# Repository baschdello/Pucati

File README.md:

# Pucati
Pump controller with adjustable timer

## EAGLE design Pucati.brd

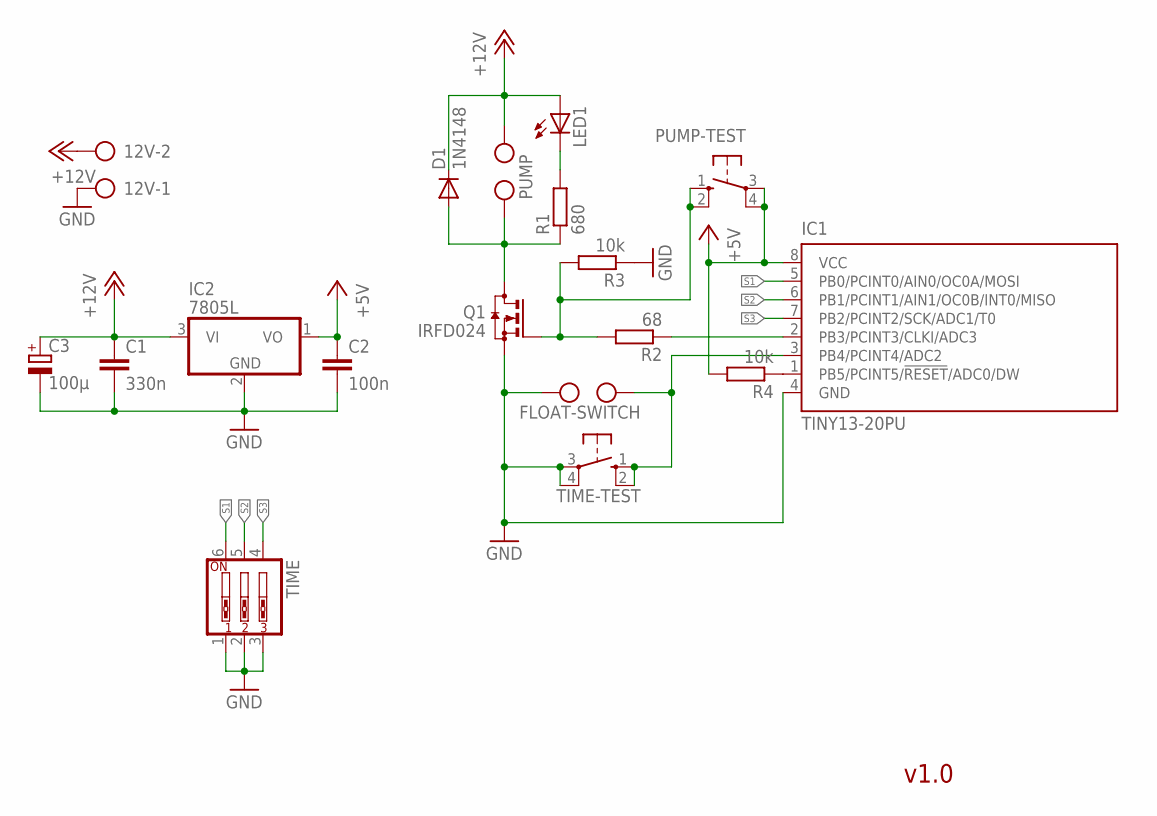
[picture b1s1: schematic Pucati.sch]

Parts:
12V: AK500/2
C1: 330n; C1206
C2: 100n; C1206
C3: 100µ; E2,5-5
D1: 1N4148; DO35-10
FLOAT-SWITCH: AK500/2
IC1: TINY13-20PU; DIL08
IC2: 7805L; TO92
LED1: LED5MM
PUMP: AK500/2
PUMP-TEST: 10-XX; B3F-10XX
Q1: IRFD024; C370-01
R1: 680; R1206
R2: 68; R1206
R3, R4: 10k; R1206
TIME: SW_DIP-3; EDG-03
TIME-TEST: 10-XX; B3F-10XX

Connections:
+5V: C2.1, IC1.8 (VCC), IC2.1 (VO), PUMP-TEST.3, PUMP-TEST.4 (P1), R4.2
+12V: 12V.2, C1.1, C3.+, D1.C, IC2.3 (VI), LED1.A, PUMP.2
GND: 12V.1, C1.2, C2.2, C3.-, FLOAT-SWITCH.2, IC1.4 (GND), IC2.2 (GND), Q1.S, R3.1, TIME.1, TIME.2, TIME.3, TIME-TEST.3, TIME-TEST.4 (P1)
unnamed: IC1.1 (PB5/PCINT5/!RESET!/ADC0/DW), R4.1
unnamed: D1.A, PUMP.1, Q1.D, Q1.D1 (D), R1.1
unnamed: LED1.K (C), R1.2
unnamed: FLOAT-SWITCH.1, IC1.3 (PB4/PCINT4/ADC2), TIME-TEST.1 (S), TIME-TEST.2 (S1)
unnamed: IC1.2 (PB3/PCINT3/CLKI/ADC3), R2.1
unnamed: PUMP-TEST.1 (S), PUMP-TEST.2 (S1), Q1.G, R2.2, R3.2
S1: IC1.5 (PB0/PCINT0/AIN0/OC0A/MOSI), TIME.6
S2: IC1.6 (PB1/PCINT1/AIN1/OC0B/INT0/MISO), TIME.5
S3: IC1.7 (PB2/PCINT2/SCK/ADC1/T0), TIME.4

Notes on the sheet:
FLOAT-SWITCH
PUMP
v1.0

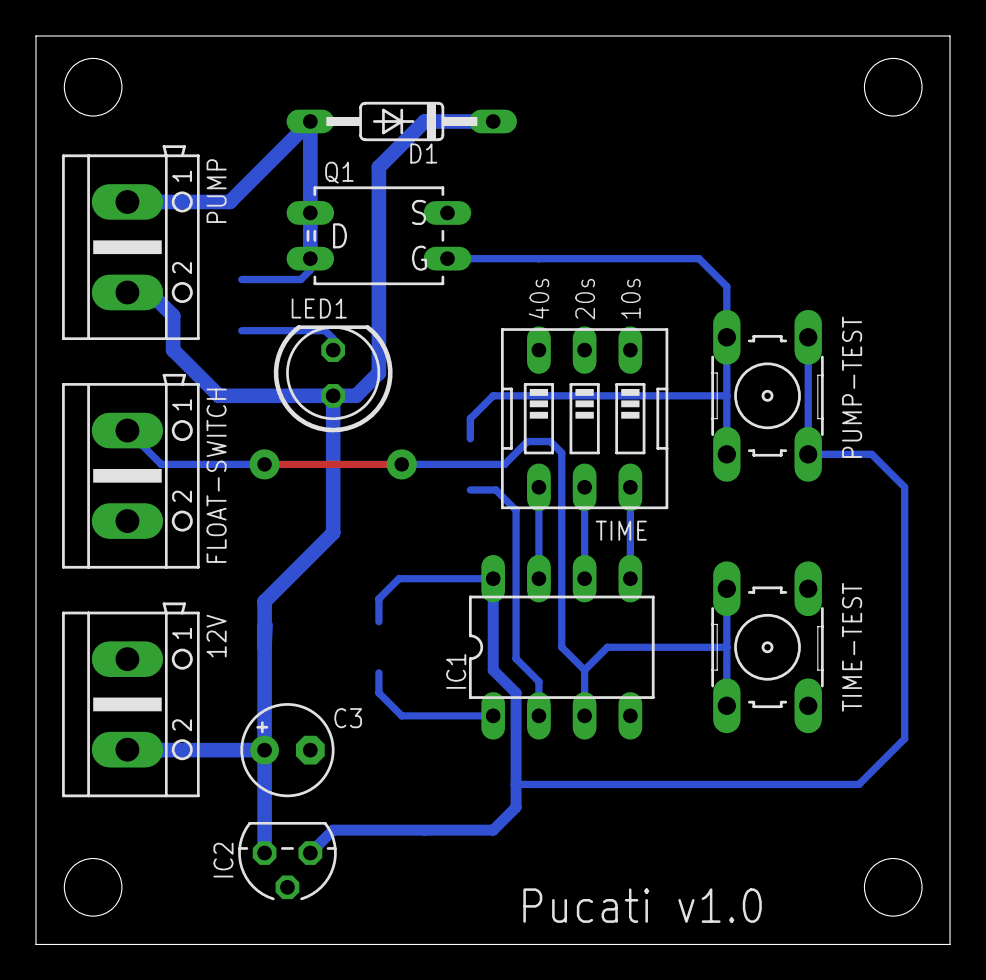
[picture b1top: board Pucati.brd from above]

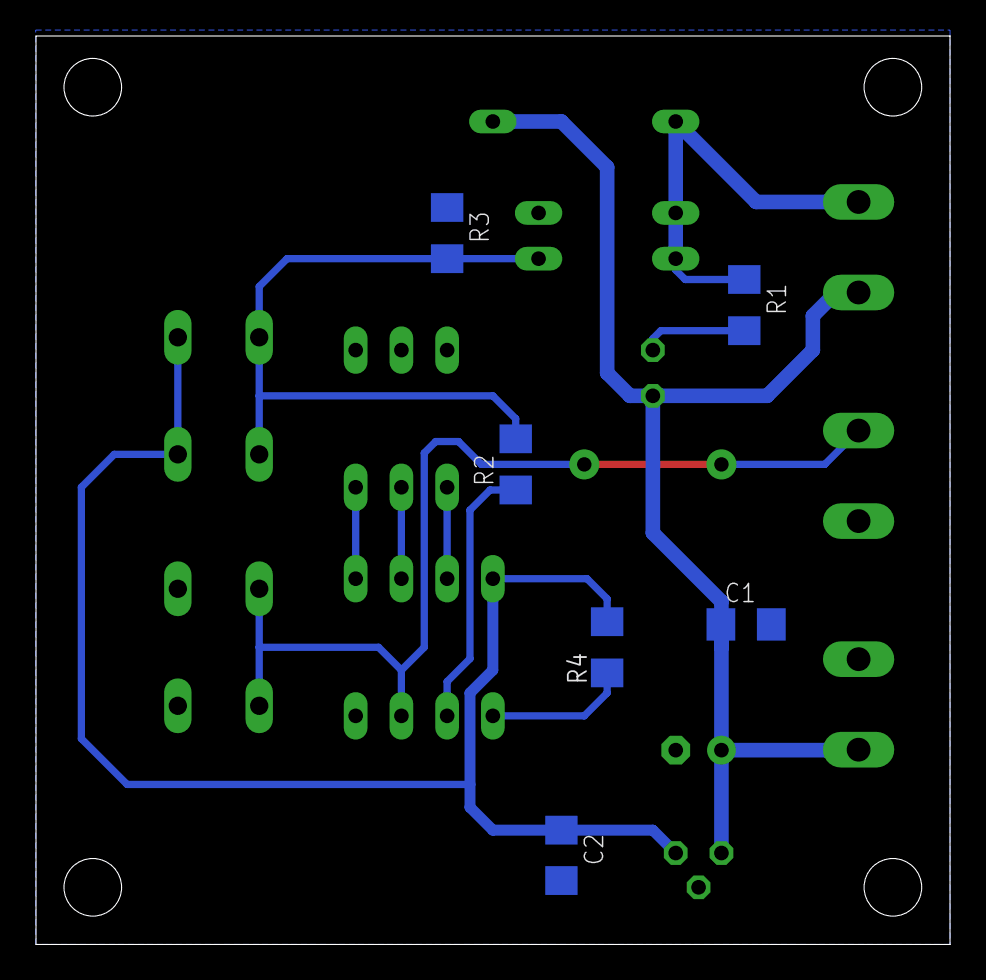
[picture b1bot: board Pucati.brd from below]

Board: 2 copper layers, 50.8 x 50.5 mm, 18 parts (6 on the bottom side), 12 nets.

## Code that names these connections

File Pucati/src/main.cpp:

#include <Arduino.h>
#include <Ticker.h>

#define WATERPUMP     PB3
#define FLOATSWITCH   PB4

volatile uint8_t lock;
volatile uint8_t time;
void timerISR();
Ticker timer(timerISR, 1000);

void setup() {
  // put your setup code here, to run once:
  pinMode(PB0,INPUT_PULLUP);
  pinMode(PB1,INPUT_PULLUP);
  pinMode(PB2,INPUT_PULLUP);
  digitalWrite(WATERPUMP,HIGH);
  pinMode(FLOATSWITCH,INPUT_PULLUP);
  //timer.interval(1000); //ms
  timer.stop();
  wdt_enable(WDTO_1S);
}

void timerISR() {
  if(time-- == 0) {
    pinMode(WATERPUMP,INPUT);
    timer.stop();
    lock = 0;
  }
}

void loop() {
  // put your main code here, to run repeatedly:

  if(!digitalRead(FLOATSWITCH) && !lock)
  {
    time = !digitalRead(PB2)*40 + !digitalRead(PB1)*20 + !digitalRead(PB0)*10;
    pinMode(WATERPUMP,OUTPUT);
    timer.start();
    lock = 1;
  }

  wdt_reset();
  timer.update();
}

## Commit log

2020-08-06 Fixed input levels
